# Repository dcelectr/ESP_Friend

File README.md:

# ESP_Friend
Adapter board to be used with the Adafruit CP2104 Friend (Product ID: 3309)  to program M5Stack products such as UNIT CAM/STAMP series, etc.

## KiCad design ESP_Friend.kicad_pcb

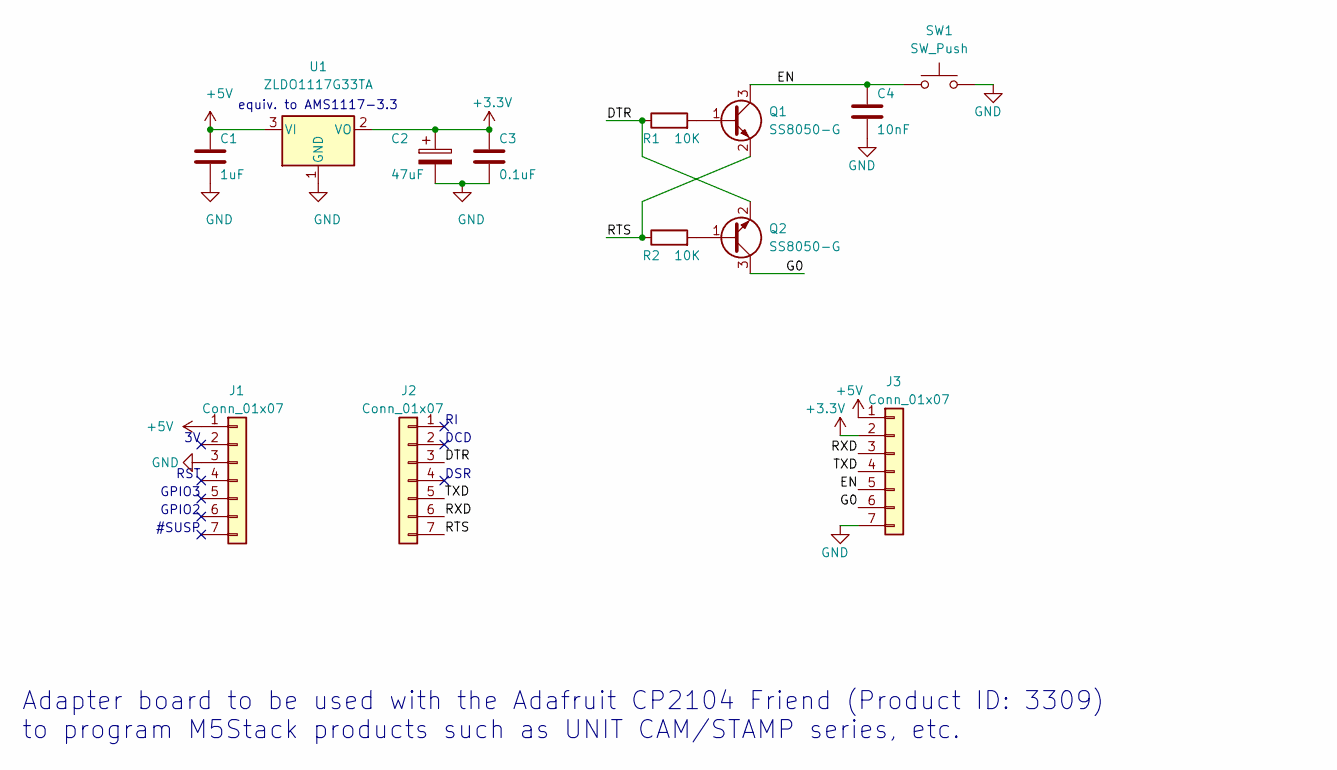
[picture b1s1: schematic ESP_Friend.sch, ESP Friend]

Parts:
C1: 1uF; C_0805_2012Metric_Pad1.18x1.45mm_HandSolder
C2: 47uF; CP_EIA-3216-10_Kemet-I_Pad1.58x1.35mm_HandSolder
C3: 0.1uF; C_0805_2012Metric_Pad1.18x1.45mm_HandSolder
C4: 10nF; C_0805_2012Metric_Pad1.18x1.45mm_HandSolder
J1, J2: Conn_01x07; PinHeader_1x07_P2.54mm_Vertical
J3: Conn_01x07; PinHeader_1x07_P2.54mm_Horizontal
Q1, Q2: SS8050-G; SOT-23_Handsoldering
R1, R2: 10K; R_0805_2012Metric_Pad1.20x1.40mm_HandSolder
SW1: SW_Push; SW_SPST_B3U-1000P
U1: ZLDO1117G33TA; SOT-223-3_TabPin2

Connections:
+3V3: C2.1, C3.1, J3.2, U1.2 (VO)
+5V: C1.1, J1.1, J3.1, U1.3 (VI)
/DTR: J2.3, Q2.2 (E), R1.1
/EN: C4.1, J3.5, Q1.3 (C), SW1.1
/G0: J3.6, Q2.3 (C)
/RTS: J2.7, Q1.2 (E), R2.1
/RXD: J2.6, J3.3
/TXD: J2.5, J3.4
GND: C1.2, C2.2, C3.2, C4.2, J1.3, J3.7, SW1.2, U1.1 (GND)
unnamed: Q1.1 (B), R1.2
unnamed: Q2.1 (B), R2.2

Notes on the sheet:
DSR
RST
GPIO3
GPIO2
#SUSP
equiv. to AMS1117-3.3
DCD
Adapter board to be used with the Adafruit CP2104 Friend (Product ID: 3309) to program M5Stack products such as UNIT CAM/STAMP series, etc.

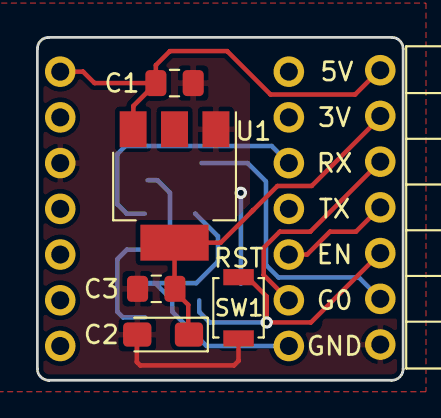
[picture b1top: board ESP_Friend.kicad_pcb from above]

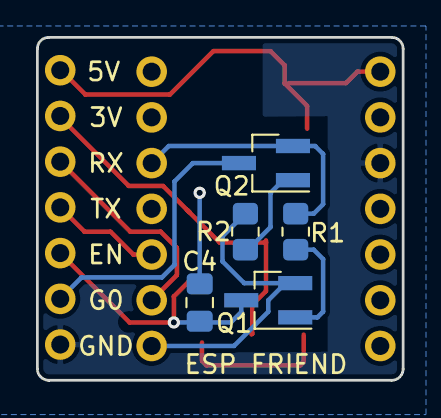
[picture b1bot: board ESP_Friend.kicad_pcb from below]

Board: 2 copper layers, 20.3 x 19.1 mm, 13 parts (7 on the bottom side), 11 nets.
